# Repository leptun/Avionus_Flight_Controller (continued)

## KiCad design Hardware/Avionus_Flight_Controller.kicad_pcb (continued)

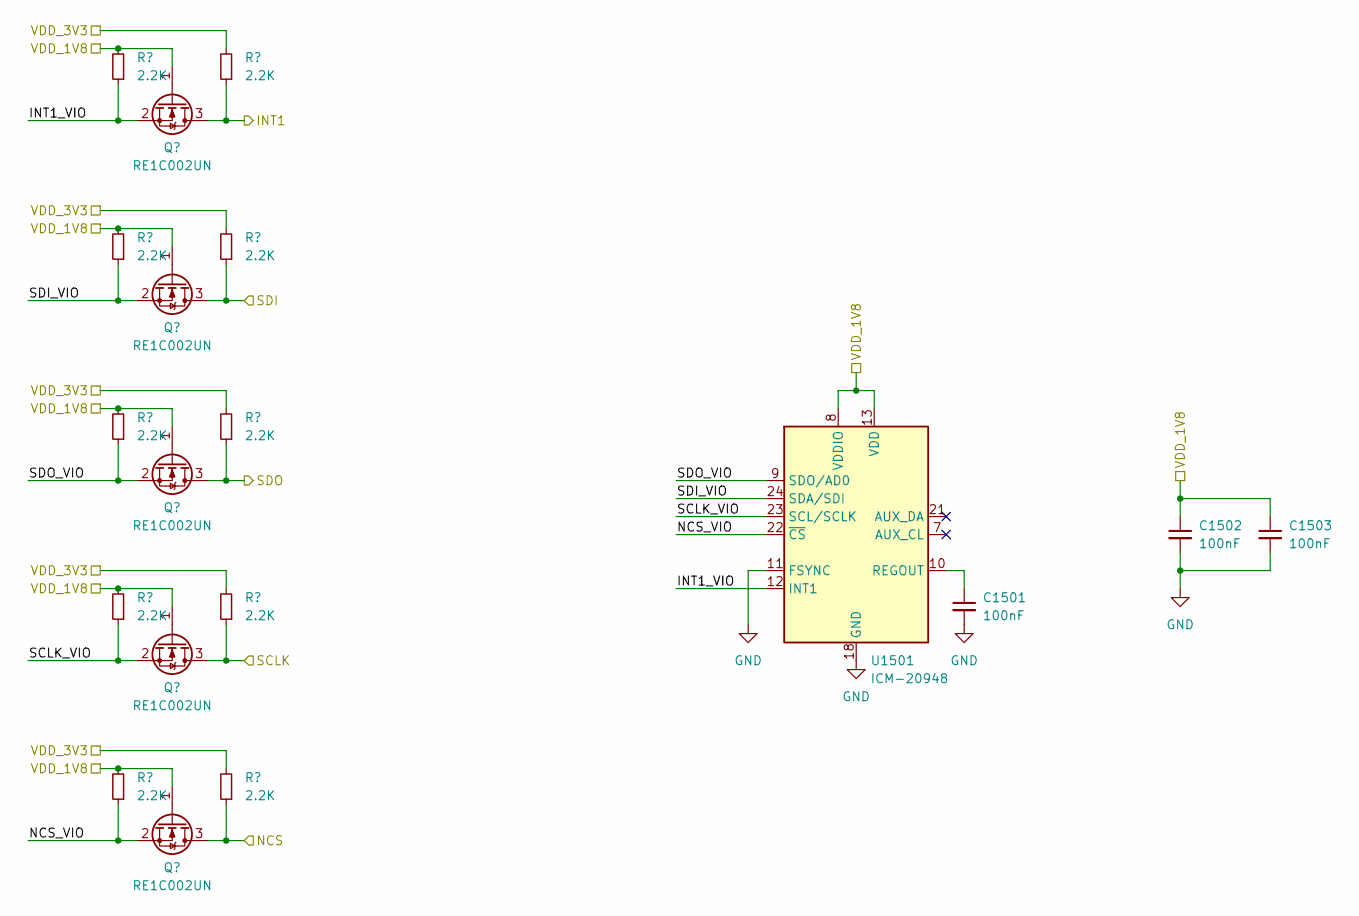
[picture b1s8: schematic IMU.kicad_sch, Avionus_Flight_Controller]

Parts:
C1501, C1502, C1503: 100nF; C_0603_1608Metric
Q1501, Q1502, Q1503, Q1504, Q1505: RE1C002UN; SOT-416
R1501, R1502, R1503, R1504, R1505, R1506, R1507, R1508, R1509, R1510: 2.2K; R_0805_2012Metric
U1501: ICM-20948; InvenSense_QFN-24_3x3mm_P0.4mm

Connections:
/GPS/VCC: R1506.2, R1507.2, R1508.2, R1509.2, R1510.2; also elsewhere on the board
/IMU/INT1: Q1501.3 (D), R1506.1; also elsewhere on the board
/IMU/INT1_VIO: Q1501.2 (S), R1501.1, U1501.12 (INT1)
/IMU/NCS: Q1505.3 (D), R1510.1; also elsewhere on the board
/IMU/NCS_VIO: Q1505.2 (S), R1505.1, U1501.22 (~CS)
/IMU/SCLK: Q1504.3 (D), R1509.1; also elsewhere on the board
/IMU/SCLK_VIO: Q1504.2 (S), R1504.1, U1501.23 (SCL/SCLK)
/IMU/SDI: Q1502.3 (D), R1507.1; also elsewhere on the board
/IMU/SDI_VIO: Q1502.2 (S), R1502.1, U1501.24 (SDA/SDI)
/IMU/SDO: Q1503.3 (D), R1508.1; also elsewhere on the board
/IMU/SDO_VIO: Q1503.2 (S), R1503.1, U1501.9 (SDO/AD0)
/IMU/VDD_1V8: C1502.1, C1503.1, Q1501.1 (G), Q1502.1 (G), Q1503.1 (G), Q1504.1 (G), Q1505.1 (G), R1501.2, R1502.2, R1503.2, R1504.2, R1505.2, U1501.8 (VDDIO), U1501.13 (VDD); also elsewhere on the board
GND: C1501.2, C1502.2, C1503.2, U1501.11 (FSYNC), U1501.18 (GND), U1501.20 (GND); also elsewhere on the board
unnamed: C1501.1, U1501.10 (REGOUT)

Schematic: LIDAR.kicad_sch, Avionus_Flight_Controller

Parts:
J1401: LIDAR1; PinHeader_1x08_P2.54mm_Horizontal
J1402: LIDAR2; PinHeader_1x06_P2.54mm_Horizontal
U801: USBLC6-2SC6; SOT-23-6
U1401: USBLC6-4SC6; SOT-23-6

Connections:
/GPS/SCL: J1401.1, J1402.3, U1401.6 (I/O4); also elsewhere on the board
/GPS/SDA: J1401.2, J1402.4, U1401.4 (I/O3); also elsewhere on the board
/LIDAR/RX: J1401.6, U1401.1 (I/O1); also elsewhere on the board
/LIDAR/TX/DATA_READY: J1401.5, U1401.3 (I/O2); also elsewhere on the board
/USB_D+: U801.1 (I/O1); also elsewhere on the board
/USB_D-: U801.3 (I/O2); also elsewhere on the board
GND: J1401.3, J1401.7, J1402.2, U801.2 (GND), U1401.2 (GND); also elsewhere on the board

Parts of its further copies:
U1402: USBLC6-2SC6; SOT-23-6

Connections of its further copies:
/LIDAR/GPIO1: U1402.1 (I/O1); also elsewhere on the board
/LIDAR/XSHUT: U1402.3 (I/O2); also elsewhere on the board
GND: U1402.2 (GND); also elsewhere on the board

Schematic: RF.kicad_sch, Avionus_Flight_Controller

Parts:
J901: SMA_Amphenol_132134_Vertical
U901: LAMBDA62

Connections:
/MCU/GPIO_PB10+EXTI10: U901.7 (DIO1); also elsewhere on the board
/MCU/GPIO_PB11+EXTI11: U901.8 (DIO2); also elsewhere on the board
/MCU/GPIO_PB12+EXTI12: U901.9 (DIO3); also elsewhere on the board
/MCU/GPIO_PE11: U901.16 (NSS); also elsewhere on the board
/MCU/GPIO_PE15+EXTI15: U901.6 (BUSY); also elsewhere on the board
/MCU/GPIO_PF13: U901.4 (RX_SWITCH); also elsewhere on the board
/MCU/GPIO_PF14: U901.5 (TX_SWITCH); also elsewhere on the board
/MCU/GPIO_PF15: U901.12 (~RESET); also elsewhere on the board
/MCU/SPI4_MISO: U901.14 (MISO); also elsewhere on the board
/MCU/SPI4_MOSI: U901.15 (MOSI); also elsewhere on the board
/MCU/SPI4_SCK: U901.13 (SCK); also elsewhere on the board
/POWER/D4_3V3: U901.3 (VCC); also elsewhere on the board
GND: J901.2 (Ext), U901.2 (GND); also elsewhere on the board
unnamed: J901.1 (In), U901.1 (ANT/NC)

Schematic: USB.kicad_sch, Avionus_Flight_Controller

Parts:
J801: USB_C_Receptacle_USB2.0; USB4110-GF-A
R801, R802: 5.1K; R_0603_1608Metric
TP801: TestPoint_Pad_D1.0mm
U801: USBLC6-2SC6; SOT-23-6

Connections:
/MCU/USB_OTG_HS_SOF: TP801.1; also elsewhere on the board
/USB_D+: U801.1 (I/O1); also elsewhere on the board
/USB_D-: U801.3 (I/O2); also elsewhere on the board
GND: J801.A1 (GND), J801.A12 (GND), J801.B1 (GND), J801.B12 (GND), R801.1, R802.1, U801.2 (GND); also elsewhere on the board
unnamed: J801.A5 (CC1), R801.2
unnamed: J801.B5 (CC2), R802.2

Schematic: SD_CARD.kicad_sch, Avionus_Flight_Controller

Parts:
C701: 100nF; C_0603_1608Metric
J701: SD_Card; SDP-09L-SG
R701, R702, R703, R704, R705: 47K; R_0805_2012Metric
R706, R707: 2.2K; R_0805_2012Metric

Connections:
/MCU/GPIO_PG13+EXTI13: R706.2; also elsewhere on the board
/MCU/GPIO_PG14: R707.1; also elsewhere on the board
/MCU/SDMMC2_CK: J701.5 (CLK); also elsewhere on the board
/MCU/SDMMC2_CMD: J701.2 (CMD), R703.2; also elsewhere on the board
/MCU/SDMMC2_D0: J701.7 (DAT0), R702.2; also elsewhere on the board
/MCU/SDMMC2_D1: J701.8 (DAT1), R701.2; also elsewhere on the board
/MCU/SDMMC2_D2: J701.9 (DAT2), R705.2; also elsewhere on the board
/MCU/SDMMC2_D3: J701.1 (CD/DAT3), R704.2; also elsewhere on the board
/POWER/D3_3V3: C701.1, J701.4 (VDD), R701.1, R702.1, R703.1, R704.1, R705.1; also elsewhere on the board
GND: C701.2, J701.3 (VSS), J701.6 (VSS), J701.12 (SHELL1), J701.13 (SHELL2); also elsewhere on the board
unnamed: J701.10 (CARD_DETECT), R706.1
unnamed: J701.11 (WRITE_PROTECT), R707.2

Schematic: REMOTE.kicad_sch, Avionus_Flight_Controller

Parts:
J1101: PPM; PinHeader_1x03_P2.54mm_Horizontal
J1102: iBUS; PinHeader_1x03_P2.54mm_Horizontal
Q1101, Q1102: RE1C002UN; SOT-416
R1101, R1102, R1103, R1104: 2.2K; R_0805_2012Metric
U1101: USBLC6-4SC6; SOT-23-6

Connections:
/DEBUG/T_VCC: Q1101.1 (G), Q1102.1 (G), R1101.2, R1102.2; also elsewhere on the board
/MCU/TIM9_CH2: Q1101.2 (S), R1101.1; also elsewhere on the board
/MCU/UART4_TX: Q1102.2 (S), R1102.1; also elsewhere on the board
GND: J1101.1, J1102.1, U1101.2 (GND); also elsewhere on the board
unnamed: J1101.3, Q1101.3 (D), R1103.1, U1101.1 (I/O1)
unnamed: J1102.3, Q1102.3 (D), R1104.1, U1101.3 (I/O2)

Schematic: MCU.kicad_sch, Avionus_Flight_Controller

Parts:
C301, C302: 15pF; C_0805_2012Metric
C303, C304: 2.2uF; C_0805_2012Metric
C305, C306, C307, C308, C309, C310, C311, C312, C313, C314, C315, C316, C318, C319: 100nF; C_0603_1608Metric
C317: 4.7uF; C_1206_3216Metric
C320, C321: 1uF; C_0805_2012Metric
R301, R302, R303, R304: 10K; R_0603_1608Metric
SW301: RESET; SW_PUSH_6mm_H5mm
TP301, TP302, TP303, TP304, TP305, TP306, TP307, TP308, TP309, TP310: TestPoint_Pad_D1.0mm
U301: STM32F722ZETx; LQFP-144_20x20mm_P0.5mm
Y301: 24MHz; ATS240C

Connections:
/DEBUG/GNDDetect: U301.104 (PA12); also elsewhere on the board
/DEBUG/T_JCLK/T_SWCLK: U301.109 (PA14); also elsewhere on the board
/DEBUG/T_JTDI: U301.110 (PA15); also elsewhere on the board
/DEBUG/T_JTDO/T_SWO: U301.133 (PB3); also elsewhere on the board
/DEBUG/T_JTMS/T_SWDIO: U301.105 (PA13); also elsewhere on the board
/DEBUG/T_NRST: C319.2, SW301.2, U301.25 (NRST); also elsewhere on the board
/DEBUG/T_VCC: C305.1, C306.1, C307.1, C308.1, C309.1, C310.1, C311.1, C312.1, C313.1, C314.1, C315.1, C316.1, C317.1, C318.1, C320.1, C321.1, U301.17 (VDD), U301.30 (VDD), U301.32 (VREF+), U301.33 (VDDA), U301.39 (VDD), U301.52 (VDD), U301.62 (VDD), U301.72 (VDD), U301.84 (VDD), U301.95 (VDDUSB), U301.108 (VDD), U301.121 (VDDSDMMC), U301.131 (VDD), U301.143 (PDR_ON), U301.144 (VDD); also elsewhere on the board
/DEBUG/T_VCP_RX: U301.78 (PD9); also elsewhere on the board
/DEBUG/T_VCP_TX: U301.77 (PD8); also elsewhere on the board
/GPS/EXTINT: U301.118 (PD4); also elsewhere on the board
/GPS/RXD: U301.113 (PC12); also elsewhere on the board
/GPS/SCL: U301.11 (PF1); also elsewhere on the board
/GPS/SDA: U301.10 (PF0); also elsewhere on the board
/GPS/TIMEPULSE: U301.117 (PD3); also elsewhere on the board
/GPS/TXD: U301.116 (PD2); also elsewhere on the board
/GPS/V_BCKP: U301.6 (VBAT); also elsewhere on the board
/GPS/~RESET: U301.114 (PD0); also elsewhere on the board
/IMU/INT1: U301.57 (PG1); also elsewhere on the board
/IMU/NCS: U301.56 (PG0); also elsewhere on the board
/IMU/SCLK: U301.41 (PA5); also elsewhere on the board
/IMU/SDI: U301.43 (PA7); also elsewhere on the board
/IMU/SDO: U301.42 (PA6); also elsewhere on the board
/LIDAR/GPIO1: U301.93 (PG8); also elsewhere on the board
/LIDAR/RX: U301.142 (PE1); also elsewhere on the board
/LIDAR/TX/DATA_READY: U301.141 (PE0); also elsewhere on the board
/LIDAR/XSHUT: U301.92 (PG7); also elsewhere on the board
/MCU/ADC1_IN12: U301.28 (PC2); also elsewhere on the board
/MCU/ADC1_IN14: U301.44 (PC4); also elsewhere on the board
/MCU/ADC2_IN10: U301.26 (PC0); also elsewhere on the board
/MCU/ADC2_IN11: U301.27 (PC1); also elsewhere on the board
/MCU/ADC2_IN13: U301.29 (PC3); also elsewhere on the board
/MCU/ADC2_IN15: U301.45 (PC5); also elsewhere on the board
/MCU/ADC3_IN8: U301.22 (PF10); also elsewhere on the board
/MCU/ADC3_IN9: U301.13 (PF3); also elsewhere on the board
/MCU/ADC3_IN14: U301.14 (PF4); also elsewhere on the board
/MCU/ADC3_IN15: U301.15 (PF5); also elsewhere on the board
/MCU/BOOT0: R304.1, U301.138 (BOOT0)
/MCU/GPIO_PB10+EXTI10: U301.69 (PB10); also elsewhere on the board
/MCU/GPIO_PB11+EXTI11: U301.70 (PB11); also elsewhere on the board
/MCU/GPIO_PB12+EXTI12: U301.73 (PB12); also elsewhere on the board
/MCU/GPIO_PD10: U301.79 (PD10); also elsewhere on the board
/MCU/GPIO_PD11: U301.80 (PD11); also elsewhere on the board
/MCU/GPIO_PE2: U301.1 (PE2); also elsewhere on the board
/MCU/GPIO_PE3: U301.2 (PE3); also elsewhere on the board
/MCU/GPIO_PE4: U301.3 (PE4); also elsewhere on the board
/MCU/GPIO_PE5+EXTI5: U301.4 (PE5); also elsewhere on the board
/MCU/GPIO_PE11: U301.64 (PE11); also elsewhere on the board
/MCU/GPIO_PE15+EXTI15: U301.68 (PE15); also elsewhere on the board
/MCU/GPIO_PF2+EXTI2: U301.12 (PF2); also elsewhere on the board
/MCU/GPIO_PF11: U301.49 (PF11); also elsewhere on the board
/MCU/GPIO_PF12: U301.50 (PF12); also elsewhere on the board
/MCU/GPIO_PF13: U301.53 (PF13); also elsewhere on the board
/MCU/GPIO_PF14: U301.54 (PF14); also elsewhere on the board
/MCU/GPIO_PF15: U301.55 (PF15); also elsewhere on the board
/MCU/GPIO_PG4: U301.89 (PG4); also elsewhere on the board
/MCU/GPIO_PG5: U301.90 (PG5); also elsewhere on the board
/MCU/GPIO_PG6+EXTI6: U301.91 (PG6); also elsewhere on the board
/MCU/GPIO_PG13+EXTI13: U301.128 (PG13); also elsewhere on the board
/MCU/GPIO_PG14: U301.129 (PG14); also elsewhere on the board
/MCU/GPIO_PG15: U301.132 (PG15); also elsewhere on the board
/MCU/LOOP: R301.1, R302.1
/MCU/QUADSPI_BK1_IO0: U301.20 (PF8); also elsewhere on the board
/MCU/QUADSPI_BK1_IO1: U301.21 (PF9); also elsewhere on the board
/MCU/QUADSPI_BK1_IO2: U301.19 (PF7); also elsewhere on the board
/MCU/QUADSPI_BK1_IO3: U301.18 (PF6); also elsewhere on the board
/MCU/QUADSPI_BK1_NCS: U301.136 (PB6); also elsewhere on the board
/MCU/QUADSPI_BK2_IO0: U301.58 (PE7); also elsewhere on the board
/MCU/QUADSPI_BK2_IO1: U301.59 (PE8); also elsewhere on the board
/MCU/QUADSPI_BK2_IO2: U301.60 (PE9); also elsewhere on the board
/MCU/QUADSPI_BK2_IO3: U301.63 (PE10); also elsewhere on the board
/MCU/QUADSPI_BK2_NCS: U301.112 (PC11); also elsewhere on the board
/MCU/QUADSPI_CLK: U301.48 (PB2); also elsewhere on the board
/MCU/RTC_OUT: U301.7 (PC13); also elsewhere on the board
/MCU/SDMMC2_CK: U301.122 (PD6); also elsewhere on the board
/MCU/SDMMC2_CMD: U301.123 (PD7); also elsewhere on the board
/MCU/SDMMC2_D0: U301.124 (PG9); also elsewhere on the board
/MCU/SDMMC2_D1: U301.125 (PG10); also elsewhere on the board
/MCU/SDMMC2_D2: U301.126 (PG11); also elsewhere on the board
/MCU/SDMMC2_D3: U301.127 (PG12); also elsewhere on the board
/MCU/SPI4_MISO: U301.66 (PE13); also elsewhere on the board
/MCU/SPI4_MOSI: U301.67 (PE14); also elsewhere on the board
/MCU/SPI4_SCK: U301.65 (PE12); also elsewhere on the board
/MCU/TIM9_CH2: U301.5 (PE6); also elsewhere on the board
/MCU/TIM11_CH1: U301.140 (PB9); also elsewhere on the board
/MCU/UART4_TX: U301.111 (PC10); also elsewhere on the board
/MCU/USB_OTG_HS_SOF: U301.40 (PA4); also elsewhere on the board
/SERVO/CH0: U301.96 (PC6); also elsewhere on the board
/SERVO/CH1: U301.97 (PC7); also elsewhere on the board
/SERVO/CH2: U301.98 (PC8); also elsewhere on the board
/SERVO/CH3: U301.99 (PC9); also elsewhere on the board
/SERVO/CH4: U301.82 (PD13); also elsewhere on the board
/SERVO/CH5: U301.81 (PD12); also elsewhere on the board
/SERVO/CH6: U301.85 (PD14); also elsewhere on the board
/SERVO/CH7: U301.86 (PD15); also elsewhere on the board
/SERVO/CH8: U301.100 (PA8); also elsewhere on the board
/SERVO/CH9: U301.101 (PA9); also elsewhere on the board
/SERVO/CH10: U301.102 (PA10); also elsewhere on the board
/SERVO/CH11: U301.103 (PA11); also elsewhere on the board
/SERVO/CH12: U301.37 (PA3); also elsewhere on the board
/SERVO/CH13: U301.36 (PA2); also elsewhere on the board
/SERVO/CH14: U301.35 (PA1); also elsewhere on the board
/SERVO/CH15: U301.34 (PA0); also elsewhere on the board
/USB_D+: U301.76 (PB15); also elsewhere on the board
/USB_D-: U301.75 (PB14); also elsewhere on the board
GND: C301.1, C302.1, C303.1, C304.1, C305.2, C306.2, C307.2, C308.2, C309.2, C310.2, C311.2, C312.2, C313.2, C314.2, C315.2, C316.2, C317.2, C318.2, C319.1, C320.2, C321.2, R304.2, SW301.1, U301.16 (VSS), U301.31 (VSSA), U301.38 (VSS), U301.51 (VSS), U301.61 (VSS), U301.83 (VSS), U301.94 (VSS), U301.107 (VSS), U301.120 (VSS), U301.130 (VSS); also elsewhere on the board
unnamed: TP303.1, U301.46 (PB0)
unnamed: TP304.1, U301.47 (PB1)
unnamed: TP305.1, U301.134 (PB4)
unnamed: TP306.1, U301.135 (PB5)
unnamed: TP307.1, U301.137 (PB7)
unnamed: TP308.1, U301.139 (PB8)
unnamed: R303.2, U301.74 (PB13)
unnamed: R301.2, U301.8 (PC14)
unnamed: R302.2, U301.9 (PC15)
unnamed: TP309.1, U301.115 (PD1)
unnamed: TP310.1, U301.119 (PD5)
unnamed: TP301.1, U301.87 (PG2)
unnamed: TP302.1, U301.88 (PG3)
unnamed: C301.2, U301.23 (PH0), Y301.2
unnamed: C302.2, U301.24 (PH1), Y301.1
unnamed: C303.2, U301.71 (VCAP_1)
unnamed: C304.2, U301.106 (VCAP_2)

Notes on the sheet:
VDDSDMMC
VDD
VDDA

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
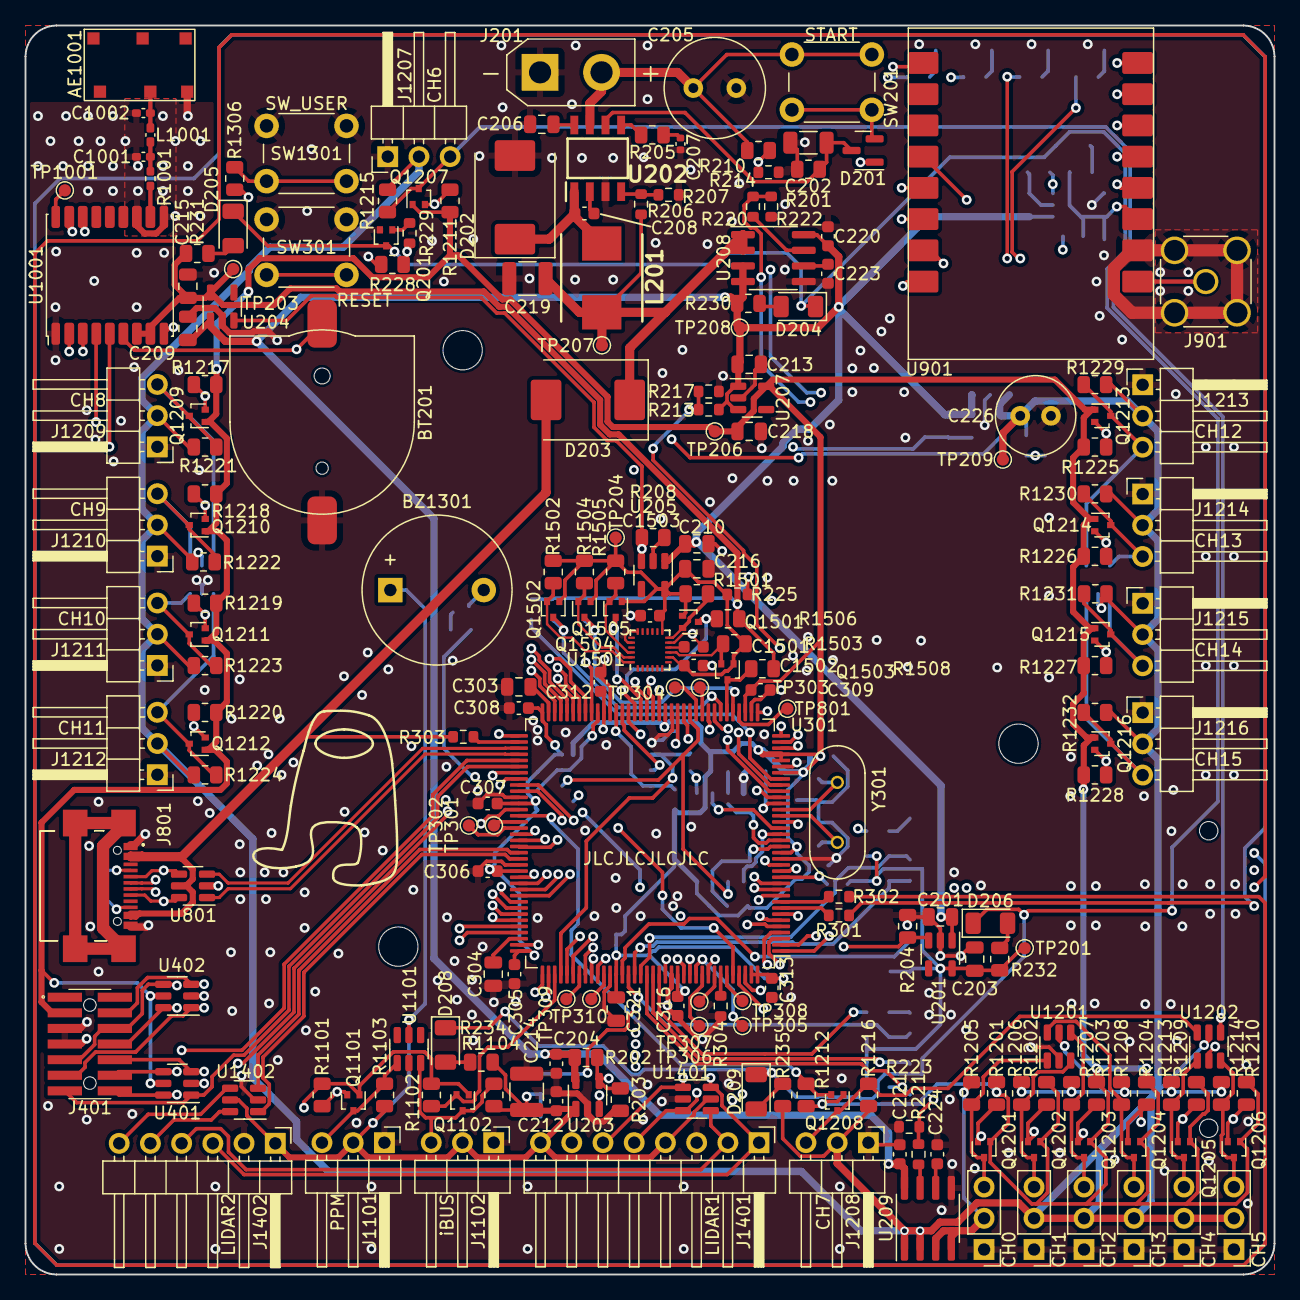
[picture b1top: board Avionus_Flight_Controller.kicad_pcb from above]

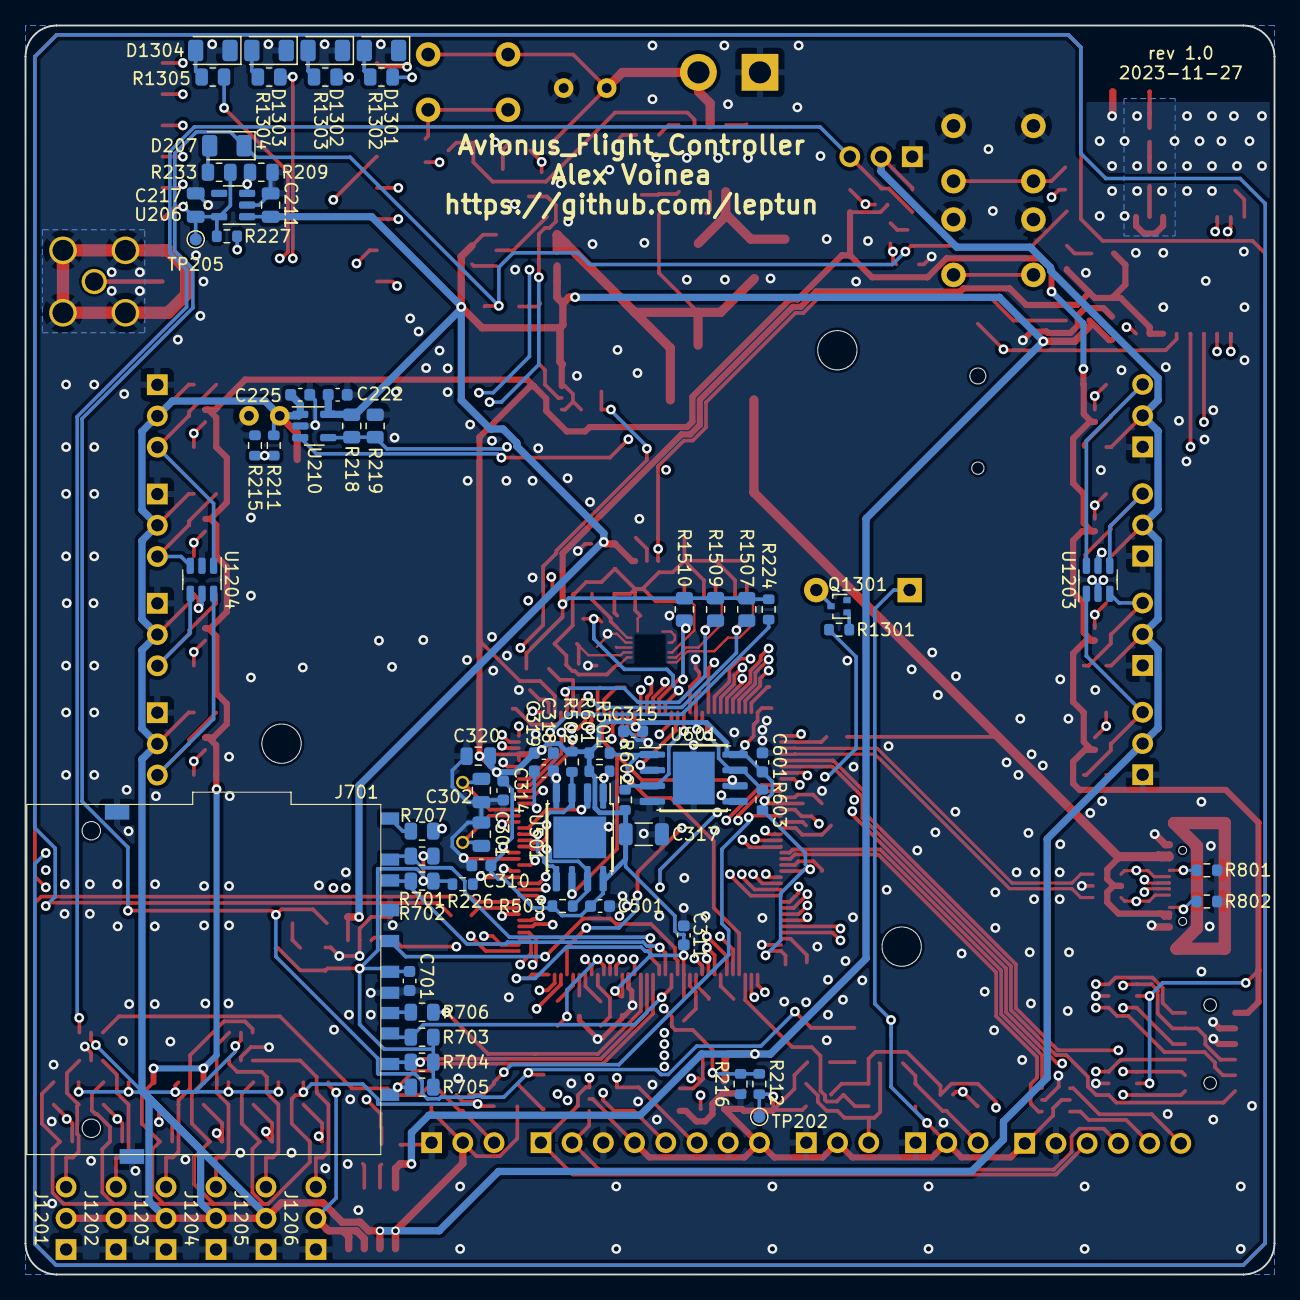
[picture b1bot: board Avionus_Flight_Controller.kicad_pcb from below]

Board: 4 copper layers, 101.6 x 101.6 mm, 287 parts (68 on the bottom side), 197 nets.

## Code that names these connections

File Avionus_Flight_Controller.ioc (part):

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Mcu.Name=STM32F722Z(C-E)Tx
Mcu.Package=LQFP144
Mcu.UserName=STM32F722ZETx
PA0-WKUP.Signal=S_TIM2_CH1_ETR
PA1.Signal=S_TIM2_CH2
PA10.Signal=S_TIM1_CH3
PA11.Signal=S_TIM1_CH4
PA12.GPIOParameters=GPIO_Label
PA12.GPIO_Label=DEBUG_GNDDetect
PA12.Signal=GPIO_Input
PA13.Mode=Trace_Asynchronous_SW
PA13.Signal=SYS_JTMS-SWDIO
PA14.Mode=Trace_Asynchronous_SW
PA14.Signal=SYS_JTCK-SWCLK
PA15.Signal=SYS_JTDI
PA2.Signal=S_TIM2_CH3
PA3.Signal=S_TIM2_CH4
PA4.Mode=Activate_SOF_FS
PA4.Signal=USB_OTG_HS_SOF
PA5.Mode=Full_Duplex_Master
PA5.Signal=SPI1_SCK
PA6.Mode=Full_Duplex_Master
PA6.Signal=SPI1_MISO
PA7.Mode=Full_Duplex_Master
PA7.Signal=SPI1_MOSI
PA8.Signal=S_TIM1_CH1
PA9.Signal=S_TIM1_CH2
PB10.GPIOParameters=GPIO_Label
PB10.GPIO_Label=RF_DIO1
PB10.Signal=GPXTI10
PB11.GPIOParameters=GPIO_Label
PB11.GPIO_Label=RF_DIO2
PB11.Signal=GPXTI11
PB12.GPIOParameters=GPIO_Label
PB12.GPIO_Label=RF_DIO3
PB12.Signal=GPXTI12
PB13.Mode=Activate_VBUS_FS
PB13.Signal=USB_OTG_HS_VBUS
PB14.Mode=Internal_Phy_Device
PB14.Signal=USB_OTG_HS_DM
PB15.Mode=Internal_Phy_Device
PB15.Signal=USB_OTG_HS_DP
PB2.Mode=Dual_Bank
PB2.Signal=QUADSPI_CLK
PB3.Mode=Trace_Asynchronous_SW
PB3.Signal=SYS_JTDO-SWO
PB6.Mode=Enable Chip Select for each bank
PB6.Signal=QUADSPI_BK1_NCS
PB9.GPIOParameters=GPIO_Label
PB9.GPIO_Label=UI_BUZZER
PB9.Signal=S_TIM11_CH1
PC0.Signal=SharedAnalog_PC0
PC1.Signal=SharedAnalog_PC1
PC10.GPIOParameters=GPIO_Label
PC10.GPIO_Label=REMOTE_iBUS
PC10.Mode=Half_duplex(single_wire_mode)
PC10.Signal=UART4_TX
PC11.Mode=Enable Chip Select for each bank
PC11.Signal=QUADSPI_BK2_NCS
PC12.GPIOParameters=GPIO_Label
PC12.GPIO_Label=GPS_TX
PC12.Mode=Asynchronous
PC12.Signal=UART5_TX
PC13.GPIOParameters=GPIO_Label
PC13.GPIO_Label=POWER_D1_EN
PC13.Mode=WakeUpAF1
PC13.Signal=RTC_OUT
PC14-OSC32_IN.Mode=LSE-External-Oscillator
PC14-OSC32_IN.Signal=RCC_OSC32_IN
PC15-OSC32_OUT.Mode=LSE-External-Oscillator
PC15-OSC32_OUT.Signal=RCC_OSC32_OUT
PC2.Signal=SharedAnalog_PC2
PC3.Signal=SharedAnalog_PC3
PC4.Signal=SharedAnalog_PC4
PC5.Signal=SharedAnalog_PC5
PC6.Signal=SharedStack_PC6
PC6.Stacked=true
PC7.Signal=S_TIM3_CH2
PC8.Signal=S_TIM3_CH3
PC9.Signal=S_TIM3_CH4
PD0.GPIOParameters=GPIO_Label
PD0.GPIO_Label=GPS_NRESET
PD0.Signal=GPIO_Output
PD10.GPIOParameters=GPIO_Label
PD10.GPIO_Label=UI_LED_RX
PD10.Signal=GPIO_Output
PD11.GPIOParameters=GPIO_Label
PD11.GPIO_Label=UI_LED_TX
PD11.Signal=GPIO_Output
PD12.Signal=S_TIM4_CH1
PD13.Signal=S_TIM4_CH2
PD14.Signal=S_TIM4_CH3
PD15.Signal=S_TIM4_CH4
PD2.GPIOParameters=GPIO_Label
PD2.GPIO_Label=GPS_RX
PD2.Mode=Asynchronous
PD2.Signal=UART5_RX
PD3.GPIOParameters=GPIO_Label
PD3.GPIO_Label=GPS_TIMEPULSE
PD3.Signal=GPXTI3
PD4.GPIOParameters=GPIO_Label
PD4.GPIO_Label=GPS_EXTINT
PD4.Signal=GPXTI4
PD6.Mode=SD_4_bits_Wide_bus
PD6.Signal=SDMMC2_CK
PD7.Mode=SD_4_bits_Wide_bus
PD7.Signal=SDMMC2_CMD
PD8.GPIOParameters=GPIO_Label
PD8.GPIO_Label=DEBUG_TX
PD8.Mode=Asynchronous
PD8.Signal=USART3_TX
PD9.GPIOParameters=GPIO_Label
PD9.GPIO_Label=DEBUG_RX
PD9.Mode=Asynchronous
PD9.Signal=USART3_RX
PE0.GPIOParameters=GPIO_Label
PE0.GPIO_Label=LIDAR_RX
PE0.Signal=SharedStack_PE0
PE0.Stacked=true
PE1.GPIOParameters=GPIO_Label
PE1.GPIO_Label=LIDAR_TX
PE1.Mode=Asynchronous
PE1.Signal=UART8_TX
PE10.Mode=Dual_Bank
PE10.Signal=QUADSPI_BK2_IO3
PE11.GPIOParameters=GPIO_Label
PE11.GPIO_Label=RF_NSS
PE11.Signal=GPIO_Output
PE12.Mode=Full_Duplex_Master
PE12.Signal=SPI4_SCK
PE13.Mode=Full_Duplex_Master
PE13.Signal=SPI4_MISO
PE14.Mode=Full_Duplex_Master
PE14.Signal=SPI4_MOSI
PE15.GPIOParameters=GPIO_Label
PE15.GPIO_Label=RF_BUSY
PE15.Signal=GPXTI15
PE2.GPIOParameters=GPIO_Label
PE2.GPIO_Label=UI_LED_GPS
PE2.Signal=GPIO_Output
PE3.GPIOParameters=GPIO_Label
PE3.GPIO_Label=UI_LED_STATUS
PE3.Signal=GPIO_Output
PE4.GPIOParameters=GPIO_Label
PE4.GPIO_Label=POWER_D5_EN
PE4.Signal=GPIO_Output
PE5.GPIOParameters=GPIO_Label
PE5.GPIO_Label=POWER_D5_nFAULT
PE5.Signal=GPXTI5
PE6.GPIOParameters=GPIO_Label
PE6.GPIO_Label=REMOTE_PPM
PE6.Signal=S_TIM9_CH2
PE7.Mode=Dual_Bank
PE7.Signal=QUADSPI_BK2_IO0
PE8.Mode=Dual_Bank
PE8.Signal=QUADSPI_BK2_IO1
PE9.Mode=Dual_Bank
PE9.Signal=QUADSPI_BK2_IO2
PF0.Mode=I2C
PF0.Signal=I2C2_SDA
PF1.Mode=I2C
PF1.Signal=I2C2_SCL
PF10.Signal=SharedAnalog_PF10
PF11.GPIOParameters=GPIO_Label
PF11.GPIO_Label=POWER_D2_EN
PF11.Signal=GPIO_Output
PF12.GPIOParameters=GPIO_Label
PF12.GPIO_Label=POWER_D4_EN
PF12.Signal=GPIO_Output
PF13.GPIOParameters=GPIO_Label
PF13.GPIO_Label=RF_RX_SWITCH
PF13.Signal=GPIO_Output
PF14.GPIOParameters=GPIO_Label
PF14.GPIO_Label=RF_TX_SWITCH
PF14.Signal=GPIO_Output
PF15.GPIOParameters=GPIO_Label
PF15.GPIO_Label=RF_NRESET
PF15.Signal=GPIO_Output
PF2.GPIOParameters=GPIO_Label
PF2.GPIO_Label=UI_SW_USER
PF2.Signal=GPXTI2
PF3.Signal=SharedAnalog_PF3
PF4.Signal=SharedAnalog_PF4
PF5.Signal=SharedAnalog_PF5
PF6.Mode=Dual_Bank
PF6.Signal=QUADSPI_BK1_IO3
PF7.Mode=Dual_Bank
PF7.Signal=QUADSPI_BK1_IO2
PF8.Mode=Dual_Bank
PF8.Signal=QUADSPI_BK1_IO0
PF9.Mode=Dual_Bank
PF9.Signal=QUADSPI_BK1_IO1
PG0.GPIOParameters=GPIO_Label
PG0.GPIO_Label=IMU_NSS
PG0.Signal=GPIO_Output
PG1.GPIOParameters=GPIO_Label
PG1.GPIO_Label=IMU_INT1
PG1.Signal=GPXTI1
PG10.Mode=SD_4_bits_Wide_bus
PG10.Signal=SDMMC2_D1
PG11.Mode=SD_4_bits_Wide_bus
PG11.Signal=SDMMC2_D2
PG12.Mode=SD_4_bits_Wide_bus
PG12.Signal=SDMMC2_D3
PG13.GPIOParameters=GPIO_Label
PG13.GPIO_Label=SD_CD
PG13.Signal=GPXTI13
PG14.GPIOParameters=GPIO_Label
PG14.GPIO_Label=SD_WP
PG14.Signal=GPIO_Input
PG15.GPIOParameters=GPIO_Label
PG15.GPIO_Label=POWER_D3_EN
PG15.Signal=GPIO_Output
PG2.Signal=GPIO_Analog
PG4.GPIOParameters=GPIO_Label
PG4.GPIO_Label=POWER_LEDs_EN
PG4.Signal=GPIO_Output
PG5.GPIOParameters=GPIO_Label
PG5.GPIO_Label=POWER_SERVO_5V_AUX_EN
PG5.Signal=GPIO_Output
PG6.GPIOParameters=GPIO_Label
PG6.GPIO_Label=POWER_SERVO_5V_AUX_nFAULT
PG6.Signal=GPXTI6
PG7.GPIOParameters=GPIO_Label
PG7.GPIO_Label=LIDAR_XSHUT
PG7.Signal=GPIO_Output
PG8.GPIOParameters=GPIO_Label
PG8.GPIO_Label=LIDAR_GPIO1
PG8.Signal=GPXTI8
PG9.Mode=SD_4_bits_Wide_bus
PG9.Signal=SDMMC2_D0
PH0-OSC_IN.Mode=HSE-External-Oscillator
PH0-OSC_IN.Signal=RCC_OSC_IN
PH1-OSC_OUT.Mode=HSE-External-Oscillator
PH1-OSC_OUT.Signal=RCC_OSC_OUT
RCC.HSE_VALUE=24000000
RCC.SYSCLKFreq_VALUE=216000000
RCC.SYSCLKSource=RCC_SYSCLKSOURCE_PLLCLK
board=custom

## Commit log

2023-08-22 Checkpoint
2023-08-23 update kicadlibs
2023-08-24 Add stacked footprints graphic
2023-08-25 ERC fixes
2023-08-25 beautify USB
2023-08-25 Update Buck converter compensation circuitry
2023-08-25 Add power documentation
2023-08-25 Update gitignore
2023-08-25 Add IMU supply capacitors
2023-08-28 Fix RF crystal frequency
2023-08-28 IMU FSYNC to GND
2023-10-09 Checkpoint routing
2023-10-27 Finalize schematic and some more routing
2023-11-02 Misc routing
2023-11-09 Finalize RF
2023-11-09 Lots of routing
2023-11-09 Exclude NPTH clearance errors
2023-11-09 More routing
2023-11-09 Fix overlapping courtyards
2023-11-11 Schematic layout fixes
2023-11-11 Finalize routing
2023-11-11 Misc fixes
2023-11-14 Misc
2023-11-14 Add lidar2
2023-11-14 Small layout fix
2023-11-15 Change 12K resistor to 10K
2023-11-15 Change from 5V_SEL to VBUS diode
2023-11-18 Add mounting holes
2023-11-25 Finalize silkscreen
2023-11-25 Add "JLCJLCJLCJLC" text
2023-11-25 Add GND vias
2023-11-26 Move via from under screw head
2023-11-26 Minor routing improvements
2023-11-27 Fix UART8 disabled for no reason in ioc file
2023-11-27 Minor root sheet layout fixes
2023-11-27 Swap ADC connections for simultaneous power measurement
2023-11-27 Fix buzzer polarity and UI power domain notation
2023-11-27 Update release date
2023-11-27 Plot output files
2023-11-27 Plot schematic PDF
2023-11-27 Move ioc file to project root
2023-11-27 Add pictures
2023-11-28 Add license
2023-12-16 Export step file
2023-12-20 Development backplate
2023-12-22 Add LSE crystal
2023-12-22 Remove loop, mark PG2 pad as ripped
2023-12-30 Plot layout
2023-12-31 Final
